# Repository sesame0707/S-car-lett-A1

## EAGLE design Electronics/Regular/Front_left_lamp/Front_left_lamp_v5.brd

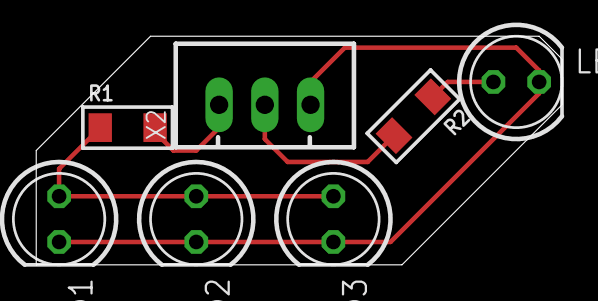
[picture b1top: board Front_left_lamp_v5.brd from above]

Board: 2 copper layers, 29.2 x 12.7 mm, 7 parts (0 on the bottom side), 5 nets.

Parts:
LED1, LED2, LED3: 2.58 V; LED5MM
LED4: 1.88 V; LED5MM
R1: 1K5; R1206
R2: 680; R1206
X2: JST-XH-03-PIN-LONG-PAD; JST-XH-03-PACKAGE-LONG-PAD

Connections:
API_START_ENGINE: LED1.A, LED2.A, LED3.A, R1.1
API_TURN_LEFT: R2.2, X2.2
GND: LED1.K, LED2.K, LED3.K, LED4.K, X2.3
unnamed: R1.2, X2.1
unnamed: LED4.A, R2.1

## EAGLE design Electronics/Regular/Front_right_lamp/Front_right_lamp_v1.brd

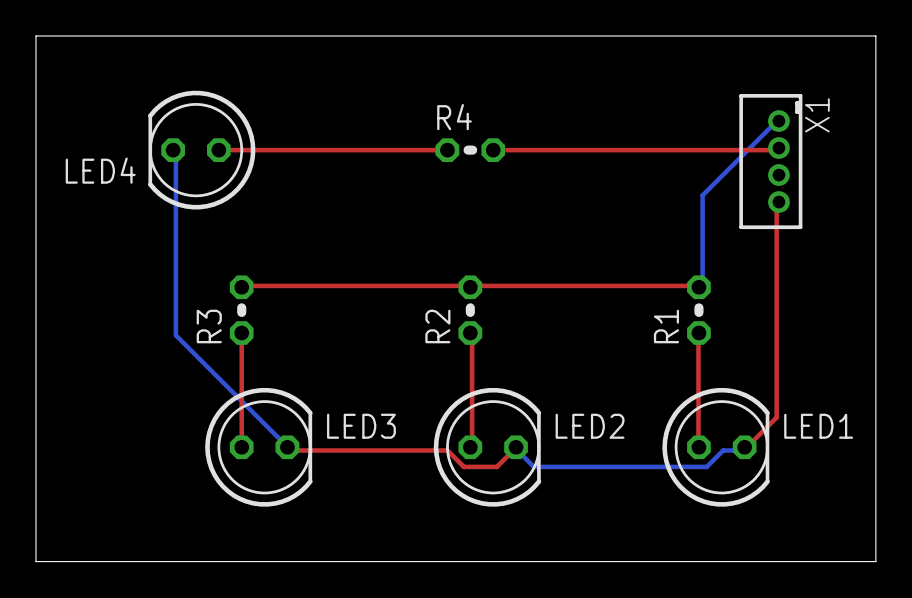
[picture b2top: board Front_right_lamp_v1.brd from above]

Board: 2 copper layers, 46.7 x 29.2 mm, 9 parts (0 on the bottom side), 7 nets.

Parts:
LED1, LED2, LED3: 2.58 V; LED5MM
LED4: 1.88 V; LED5MM
R1, R2, R3: 4K7; 0204V
R4: 680; 0204V
X1: B4B-ZR

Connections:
unnamed: LED1.A, R1.1
unnamed: LED2.A, R2.1
unnamed: LED3.A, R3.1
unnamed: LED4.A, R4.1
unnamed: R1.2, R2.2, R3.2, X1.1
unnamed: R4.2, X1.2
unnamed: LED1.K, LED2.K, LED3.K, LED4.K, X1.4

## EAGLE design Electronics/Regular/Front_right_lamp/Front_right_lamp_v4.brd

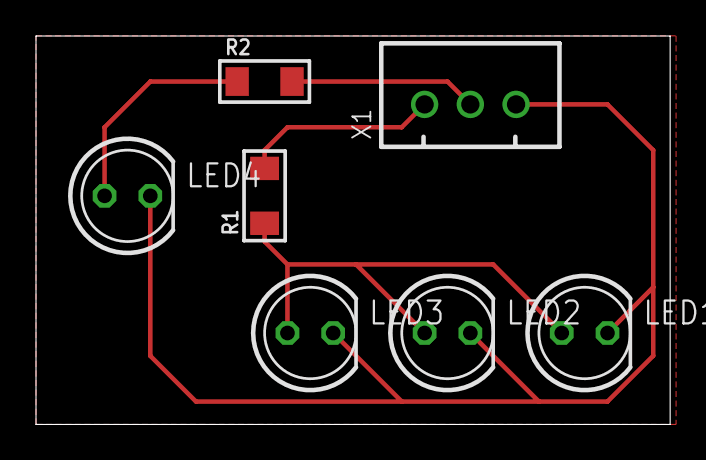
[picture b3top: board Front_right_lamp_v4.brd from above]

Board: 2 copper layers, 35.2 x 21.6 mm, 7 parts (0 on the bottom side), 5 nets.

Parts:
LED1, LED2, LED3: 2.58 V; LED5MM
LED4: 1.88 V; LED5MM
R1: 1K5; R1206
R2: 680; R1206
X1: JST-XH-03-PIN-ROUND-PAD; JST-XH-03-PACKAGE-ROUND-PAD

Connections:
API_START_ENGINE: LED1.A, LED2.A, LED3.A, R1.1
API_TURN_RIGHT: R2.2, X1.2
GND: LED1.K, LED2.K, LED3.K, LED4.K, X1.3
unnamed: LED4.A, R2.1
unnamed: R1.2, X1.1

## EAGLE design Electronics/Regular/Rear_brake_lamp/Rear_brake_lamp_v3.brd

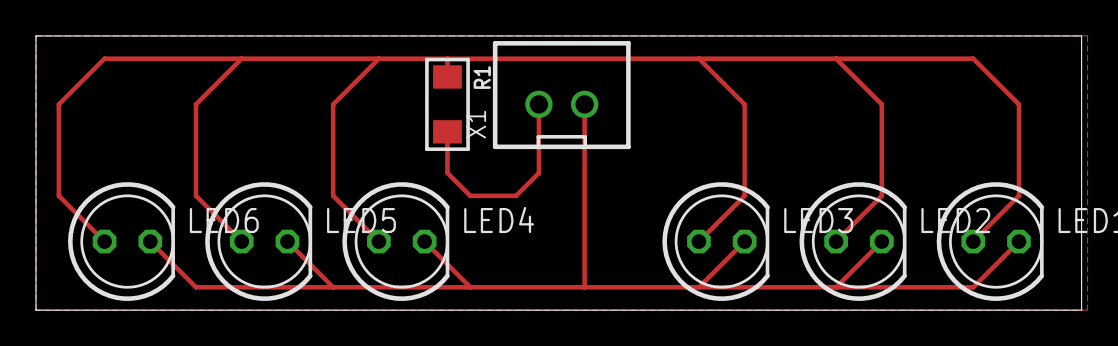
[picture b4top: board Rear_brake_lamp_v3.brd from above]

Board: 2 copper layers, 58.1 x 15.2 mm, 8 parts (0 on the bottom side), 3 nets.

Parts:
LED1, LED2, LED3, LED4, LED5, LED6: 1.78 V; LED5MM
R1: 120; R1206
X1: JST-XH-02-PIN-ROUND-PAD; JST-XH-02-PACKAGE-ROUND-PAD

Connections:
API_BRAKE: LED1.A, LED2.A, LED3.A, LED4.A, LED5.A, LED6.A, R1.1
GND: LED1.K, LED2.K, LED3.K, LED4.K, LED5.K, LED6.K, X1.2
unnamed: R1.2, X1.1

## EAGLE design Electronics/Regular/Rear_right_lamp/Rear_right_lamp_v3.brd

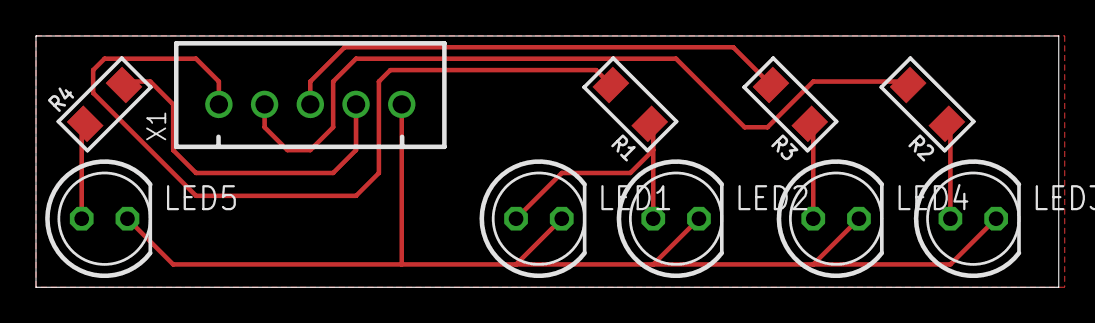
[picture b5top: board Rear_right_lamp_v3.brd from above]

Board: 2 copper layers, 56.8 x 14.0 mm, 10 parts (0 on the bottom side), 9 nets.

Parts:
LED1, LED2, LED4: 1.83 V; LED5MM
LED3: 1.88 V; LED5MM
LED5: 2.58 V; LED5MM
R1: 3K3; R1206
R2: 680; R1206
R3: 1K; R1206
R4: 4K7; R1206
X1: JST-XH-05-PIN-ROUND-PAD; JST-XH-05-PACKAGE-ROUND-PAD

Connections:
API_BREAK: R3.2, X1.3
API_START_ENGINE: LED1.A, LED2.A, R1.1
API_TURN_RIGHT: R2.2, X1.2
API_WITHDRAW: R4.2, X1.4
GND: LED1.K, LED2.K, LED3.K, LED4.K, LED5.K, X1.5
unnamed: R1.2, X1.1
unnamed: LED3.A, R2.1
unnamed: LED4.A, R3.1
unnamed: LED5.A, R4.1

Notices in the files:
parts and their libraries:
rc-master-smd: Copyright (C) 2007, Bob Starr
